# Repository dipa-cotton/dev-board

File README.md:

# dev board
This is a custom dev board I made for halflife week 5! It follows a guide but also includes an IMU sensor for things that might be useful during flight. I made this with my drone team in mind, so in the future, we can use this devboard to power everything.
# includes:
This dev board is rp2040 powered, and includes:
- A usb c port
- MCP1700
- 12 mhz crystal
- W25Q128JVS
- LSM6DSOX (IMU part)
# bom
## Bill of Materials (BOM)

| Item | Qty | Supplier | Cost/item | Total Cost | Link |
|---|---:|---|---:|---:|---|
| USB-C Receptacle | 1 | DigiKey | $1.00 | $1.00 | [DigiKey](https://www.digikey.com/en/products/detail/gct/USB4105-GF-A/11198441) |
| Surface-Mounted Capacitors | 1 | AliExpress | $3.00 | $3.00 | [AliExpress](https://www.aliexpress.com/ssr/300000512/BundleDeals2?spm=a2g0o.productlist.main.3.380266f9WEBsaM&productIds=1005012588693858:12000058767763111&pha_manifest=ssr&_immersiveMode=true&disableNav=YES&sourceName=SEARCHProduct&utparam-url=scene%3Asearch%7Cquery_from%3A%7Cx_object_id%3A1005012588693858%7C_p_origin_prod%3A1005011978546415&pvid=ddab0176-8947-4268-97fe-9c1ed6acb81d) |
| Surface-Mounted Resistors | 1 | AliExpress | $4.00 | $4.00 | [AliExpress](https://www.aliexpress.us/item/3256813168252345.html) |
| RP2040 | 1 | DigiKey | $1.00 | $1.00 | [DigiKey](https://www.digikey.com/en/products/detail/raspberry-pi/SC0914(13)/14306010) |
| MCP1700 | 1 | DigiKey | $0.50 | $0.50 | [DigiKey](https://www.digikey.com/en/products/detail/microchip-technology/MCP1700T-3302E-TT/652676) |
| 12 MHz Crystal | 1 | DigiKey | $1.00 | $1.00 | [DigiKey](https://www.digikey.com/en/products/detail/abracon-llc/ABM3C-12.000MHZ-D4Y-T/2639882) |
| W25Q128JVS | 1 | DigiKey | $1.50 | $1.50 | [DigiKey](https://www.digikey.com/en/products/detail/renesas-electronics-corporation/AT25FF321A-SHN-T/10390991) |
| LSM6DSOX | 1 | DigiKey | $6.00 | $6.00 | [DigiKey](https://www.digikey.com/en/products/detail/stmicroelectronics/LSM6DSO32XTR/14291421) |
| PCB | 1 | JLCPCB | $4.00 | $4.00 | [JLCPCB](https://jlcpcb.com) |
| Estimated Shipping | 1 | — | — | $8.00 | — |
| **Total** | | | | **$30.00** | |
# why i built this
I built this for my drone team so we can have a compact, light, small dev board that is perfect for flight, integrating an IMU without needing additional sensors.
it includes i2c!
# pictures

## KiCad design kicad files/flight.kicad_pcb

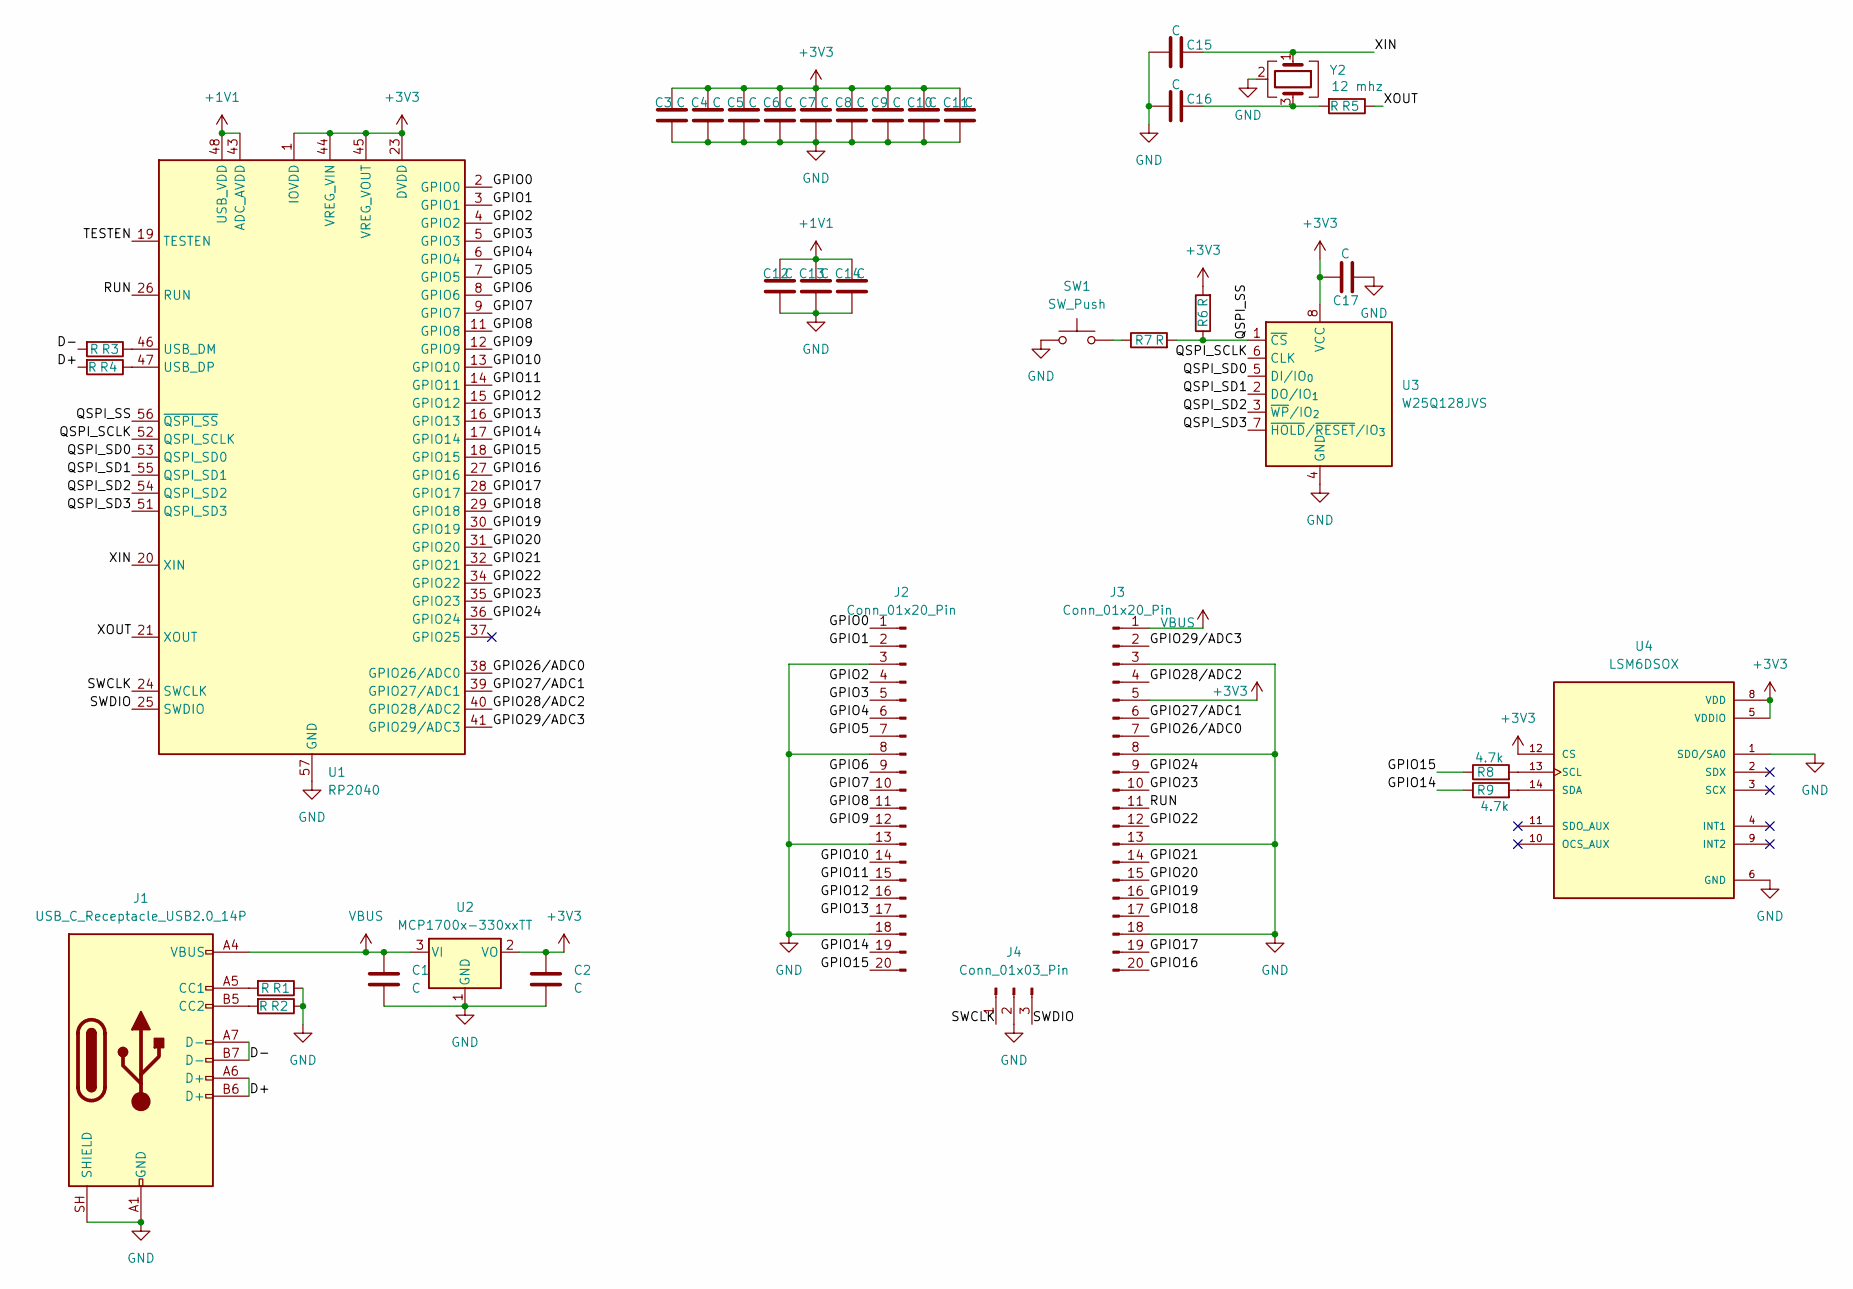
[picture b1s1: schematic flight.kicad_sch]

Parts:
C1, C2, C3, C4, C5, C6, C7, C8, C9, C10, C11, C12, C13, C14, C15, C16, C17: C; C_0201_0603Metric
J1: USB_C_Receptacle_USB2.0_14P; USB_C_Receptacle_HRO_TYPE-C-31-M-12
J2, J3: Conn_01x20_Pin; PinHeader_1x20_P2.54mm_Vertical
J4: Conn_01x03_Pin; PinHeader_1x03_P2.54mm_Vertical
R1, R2, R3, R4, R5, R6, R7: R; R_0201_0603Metric
R8, R9: 4.7k; R_0201_0603Metric
SW1: SW_Push; SW_Push_SPST_NO_Alps_SKRK
U1: RP2040; QFN-56-1EP_7x7mm_P0.4mm_EP3.2x3.2mm
U2: MCP1700x-330xxTT; SOT-23
U3: W25Q128JVS; SOIC-8_5.3x5.3mm_P1.27mm
U4: LSM6DSOX; PQFN50P250X300X86-14N; MPN LSM6DSOX
Y2: 12 mhz; Crystal_SMD_3225-4Pin_3.2x2.5mm

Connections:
+1V1: C12.1, C13.1, C14.1, U1.43 (ADC_AVDD), U1.48 (USB_VDD)
+3V3: C2.1, C3.1, C4.1, C5.1, C6.1, C7.1, C8.1, C9.1, C10.1, C11.1, C17.1, J3.5, R6.2, U1.1 (IOVDD), U1.10 (IOVDD), U1.22 (IOVDD), U1.23 (DVDD), U1.33 (IOVDD), U1.42 (IOVDD), U1.44 (VREG_VIN), U1.45 (VREG_VOUT), U1.49 (IOVDD), U1.50 (DVDD), U2.2 (VO), U3.8 (VCC), U4.5 (VDDIO), U4.8 (VDD), U4.12 (CS)
/D+: J1.A6 (D+), J1.B6 (D+), R4.2
/D-: J1.A7 (D-), J1.B7 (D-), R3.2
/GPIO0: J2.1, U1.2 (GPIO0)
/GPIO1: J2.2, U1.3 (GPIO1)
/GPIO2: J2.4, U1.4 (GPIO2)
/GPIO3: J2.5, U1.5 (GPIO3)
/GPIO4: J2.6, U1.6 (GPIO4)
/GPIO5: J2.7, U1.7 (GPIO5)
/GPIO6: J2.9, U1.8 (GPIO6)
/GPIO7: J2.10, U1.9 (GPIO7)
/GPIO8: J2.11, U1.11 (GPIO8)
/GPIO9: J2.12, U1.12 (GPIO9)
/GPIO10: J2.14, U1.13 (GPIO10)
/GPIO11: J2.15, U1.14 (GPIO11)
/GPIO12: J2.16, U1.15 (GPIO12)
/GPIO13: J2.17, U1.16 (GPIO13)
/GPIO14: J2.19, R9.1, U1.17 (GPIO14)
/GPIO15: J2.20, R8.1, U1.18 (GPIO15)
/GPIO16: J3.20, U1.27 (GPIO16)
/GPIO17: J3.19, U1.28 (GPIO17)
/GPIO18: J3.17, U1.29 (GPIO18)
/GPIO19: J3.16, U1.30 (GPIO19)
/GPIO20: J3.15, U1.31 (GPIO20)
/GPIO21: J3.14, U1.32 (GPIO21)
/GPIO22: J3.12, U1.34 (GPIO22)
/GPIO23: J3.10, U1.35 (GPIO23)
/GPIO24: J3.9, U1.36 (GPIO24)
/GPIO26/ADC0: J3.7, U1.38 (GPIO26/ADC0)
/GPIO27/ADC1: J3.6, U1.39 (GPIO27/ADC1)
/GPIO28/ADC2: J3.4, U1.40 (GPIO28/ADC2)
/GPIO29/ADC3: J3.2, U1.41 (GPIO29/ADC3)
/QSPI_SCLK: U1.52 (QSPI_SCLK), U3.6 (CLK)
/QSPI_SD0: U1.53 (QSPI_SD0), U3.5 (DI/IO_{0})
/QSPI_SD1: U1.55 (QSPI_SD1), U3.2 (DO/IO_{1})
/QSPI_SD2: U1.54 (QSPI_SD2), U3.3 (~WP/IO_{2})
/QSPI_SD3: U1.51 (QSPI_SD3), U3.7 (~HOLD/~RESET/IO_{3})
/QSPI_SS: R6.1, R7.2, U1.56 (~QSPI_SS), U3.1 (~CS)
/RUN: J3.11, U1.26 (RUN)
/SWCLK: J4.1, U1.24 (SWCLK)
/SWDIO: J4.3, U1.25 (SWDIO)
/TESTEN: U1.19 (TESTEN)
/XIN: C15.1, U1.20 (XIN), Y2.1
/XOUT: R5.1, U1.21 (XOUT)
GND: C1.2, C2.2, C3.2, C4.2, C5.2, C6.2, C7.2, C8.2, C9.2, C10.2, C11.2, C12.2, C13.2, C14.2, C15.2, C16.2, C17.2, J1.A1 (GND), J1.A12 (GND), J1.B1 (GND), J1.B12 (GND), J1.SH (SHIELD), J2.3, J2.8, J2.13, J2.18, J3.3, J3.8, J3.13, J3.18, J4.2, R1.1, R2.1, SW1.1, U1.57 (GND), U2.1 (GND), U3.4 (GND), U4.1 (SDO/SA0), U4.6 (GND), U4.7 (GND), Y2.2 (G), Y2.4 (G)
unnamed: C16.1, R5.2, Y2.3
unnamed: J1.A5 (CC1), R1.2
unnamed: J1.B5 (CC2), R2.2
unnamed: R7.1, SW1.2
unnamed: R3.1, U1.46 (USB_DM)
unnamed: R4.1, U1.47 (USB_DP)
unnamed: R8.2, U4.13 (SCL)
unnamed: R9.2, U4.14 (SDA)
VBUS: C1.1, J1.A4 (VBUS), J1.A9 (VBUS), J1.B4 (VBUS), J1.B9 (VBUS), J3.1, U2.3 (VI)

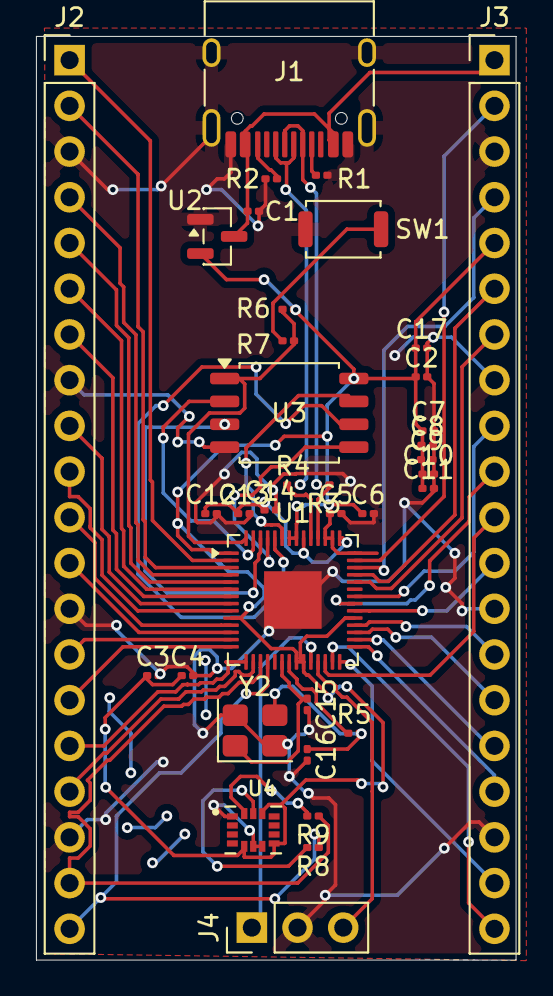
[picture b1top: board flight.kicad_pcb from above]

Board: 2 copper layers, 26.6 x 51.3 mm, 36 parts (0 on the bottom side), 54 nets.
